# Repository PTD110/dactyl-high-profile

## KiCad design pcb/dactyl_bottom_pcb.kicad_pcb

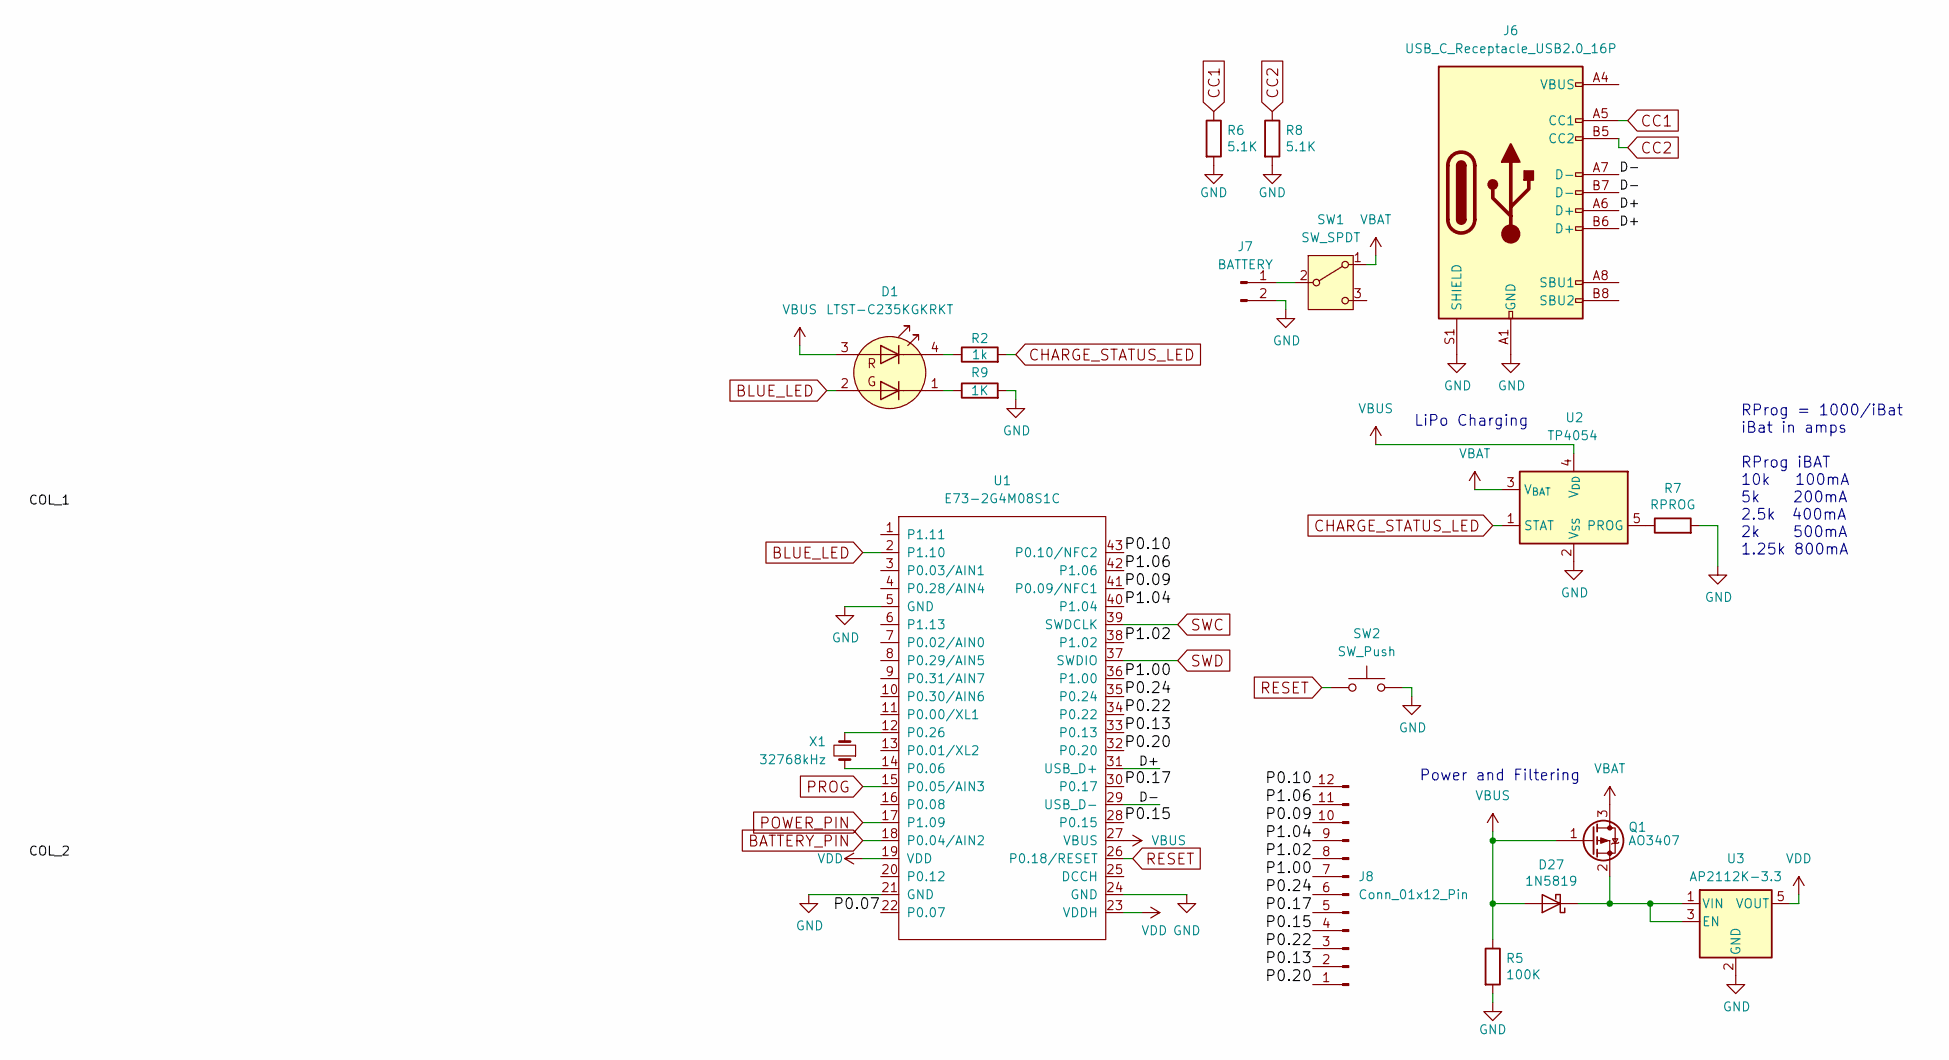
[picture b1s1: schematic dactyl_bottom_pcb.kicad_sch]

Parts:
D1: LTST-C235KGKRKT; LED_LiteOn_LTST-C235KGKRKT
D27: 1N5819; D_SOD-323F
J6: USB_C_Receptacle_USB2.0_16P; USB_C_Receptacle_GCT_USB4105-xx-A_16P_TopMnt_Horizontal
J7: BATTERY; JST_PH_S2B-PH-SM4-TB_1x02-1MP_P2.00mm_Horizontal
J8: Conn_01x12_Pin; JST_SH_SM12B-SRSS-TB_1x12-1MP_P1.00mm_Horizontal
Q1: AO3407; SOT-23
R2: 1k; R_0603_1608Metric_Pad0.98x0.95mm_HandSolder
R5: 100K; R_0603_1608Metric
R6, R8: 5.1K; R_0603_1608Metric
R7: RPROG; R_0603_1608Metric
R9: 1K; R_0603_1608Metric
SW1: SW_SPDT; SW_SP3T_PCM13
SW2: SW_Push; SW_Push_SPST_NO_Alps_SKRK
U1: E73-2G4M08S1C; E73-2G4M08S1C-52840
U2: TP4054; SOT-23-5
U3: AP2112K-3.3; SOT-23-5
X1: 32768kHz

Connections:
/D+: J6.A6 (D+), J6.B6 (D+), U1.31 (USB_D+)
/D-: J6.A7 (D-), J6.B7 (D-), U1.29 (USB_D-)
/P0.07: U1.22 (P0.07)
/P0.09: J8.10, U1.41 (P0.09/NFC1)
/P0.10: J8.12, U1.43 (P0.10/NFC2)
/P0.13: J8.2, U1.33 (P0.13)
/P0.15: J8.4, U1.28 (P0.15)
/P0.17: J8.5, U1.30 (P0.17)
/P0.20: J8.1, U1.32 (P0.20)
/P0.22: J8.3, U1.34 (P0.22)
/P0.24: J8.6, U1.35 (P0.24)
/P1.00: J8.7, U1.36 (P1.00)
/P1.02: J8.8, U1.38 (P1.02)
/P1.04: J8.9, U1.40 (P1.04)
/P1.06: J8.11, U1.42 (P1.06)
BATTERY_PIN: U1.18 (P0.04/AIN2)
BLUE_LED: D1.2 (A2), U1.2 (P1.10)
CC1: J6.A5 (CC1), R6.1
CC2: J6.B5 (CC2), R8.1
CHARGE_STATUS_LED: R2.2, U2.1 (STAT)
GND: J6.A1 (GND), J6.A12 (GND), J6.B1 (GND), J6.B12 (GND), J6.S1 (SHIELD), J7.2, R5.2, R6.2, R7.2, R8.2, R9.2, SW2.2, U1.5 (GND), U1.21 (GND), U1.24 (GND), U2.2 (V_{SS}), U3.2 (GND)
unnamed: D1.4 (K1), R2.1
unnamed: D1.1 (K2), R9.1
unnamed: D27.1 (K), Q1.2 (S), U3.1 (VIN), U3.3 (EN)
unnamed: J6.A4 (VBUS), J6.A9 (VBUS), J6.B4 (VBUS), J6.B9 (VBUS)
unnamed: J7.1, SW1.2 (B)
unnamed: U1.14 (P0.06), X1.1
unnamed: U1.12 (P0.26), X1.2
unnamed: R7.1, U2.5 (PROG)
POWER_PIN: U1.17 (P1.09)
PROG: U1.15 (P0.05/AIN3)
RESET: SW2.1, U1.26 (P0.18/RESET)
SWC: U1.39 (SWDCLK)
SWD: U1.37 (SWDIO)
VBAT: Q1.3 (D), SW1.1 (A), U2.3 (V_{BAT})
VBUS: D1.3 (A1), D27.2 (A), Q1.1 (G), R5.1, U1.27 (VBUS), U2.4 (V_{DD})
VDD: U1.19 (VDD), U1.23 (VDDH), U3.5 (VOUT)

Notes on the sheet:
Power and Filtering
LiPo Charging
RProg = 1000/iBat iBat in amps RProg iBAT 10k 100mA 5k 200mA 2.5k 400mA 2k 500mA 1.25k 800mA

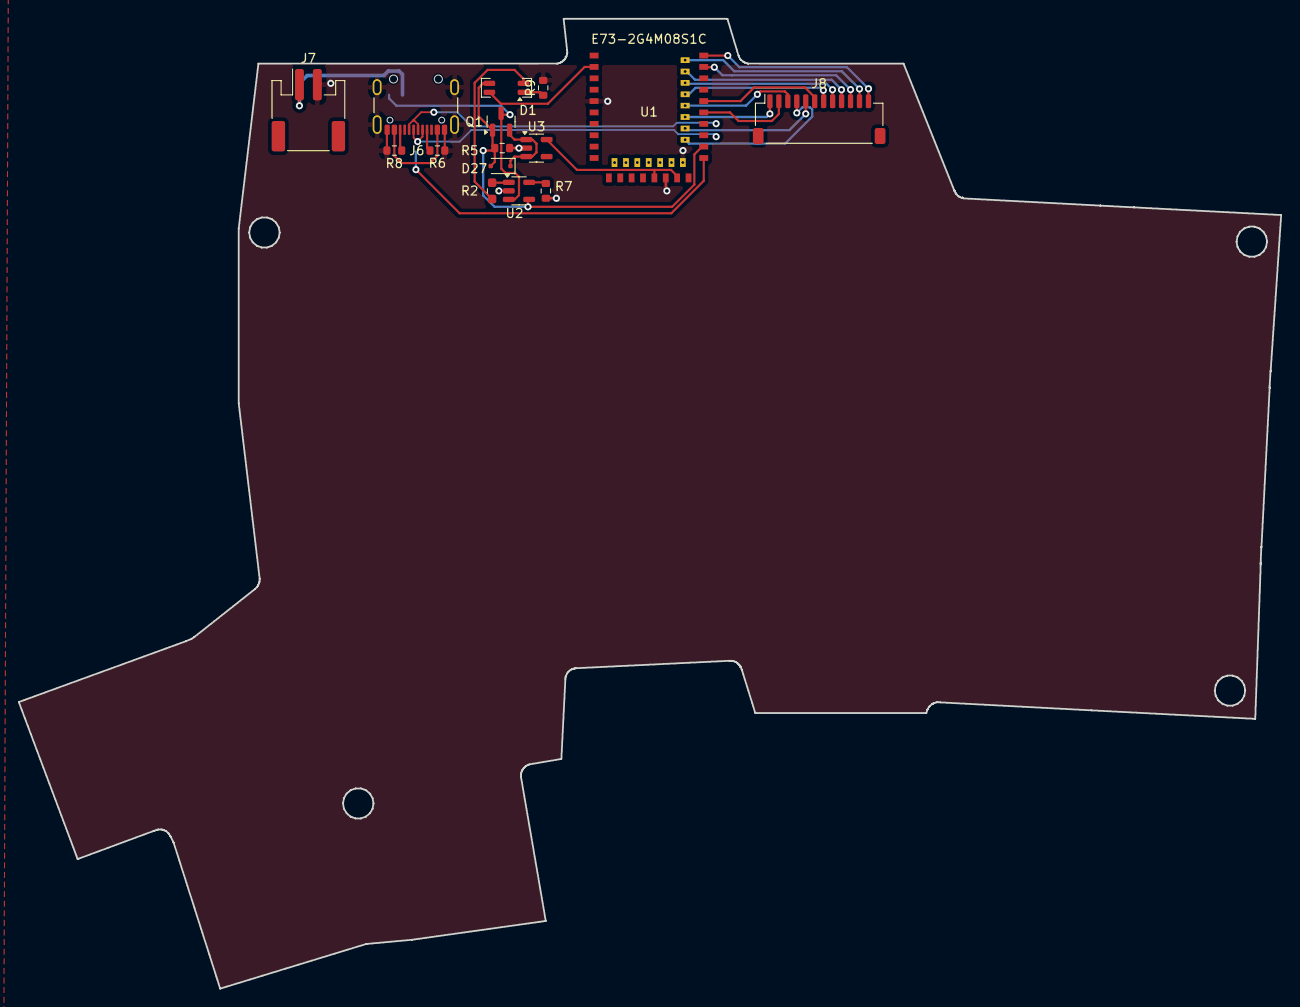
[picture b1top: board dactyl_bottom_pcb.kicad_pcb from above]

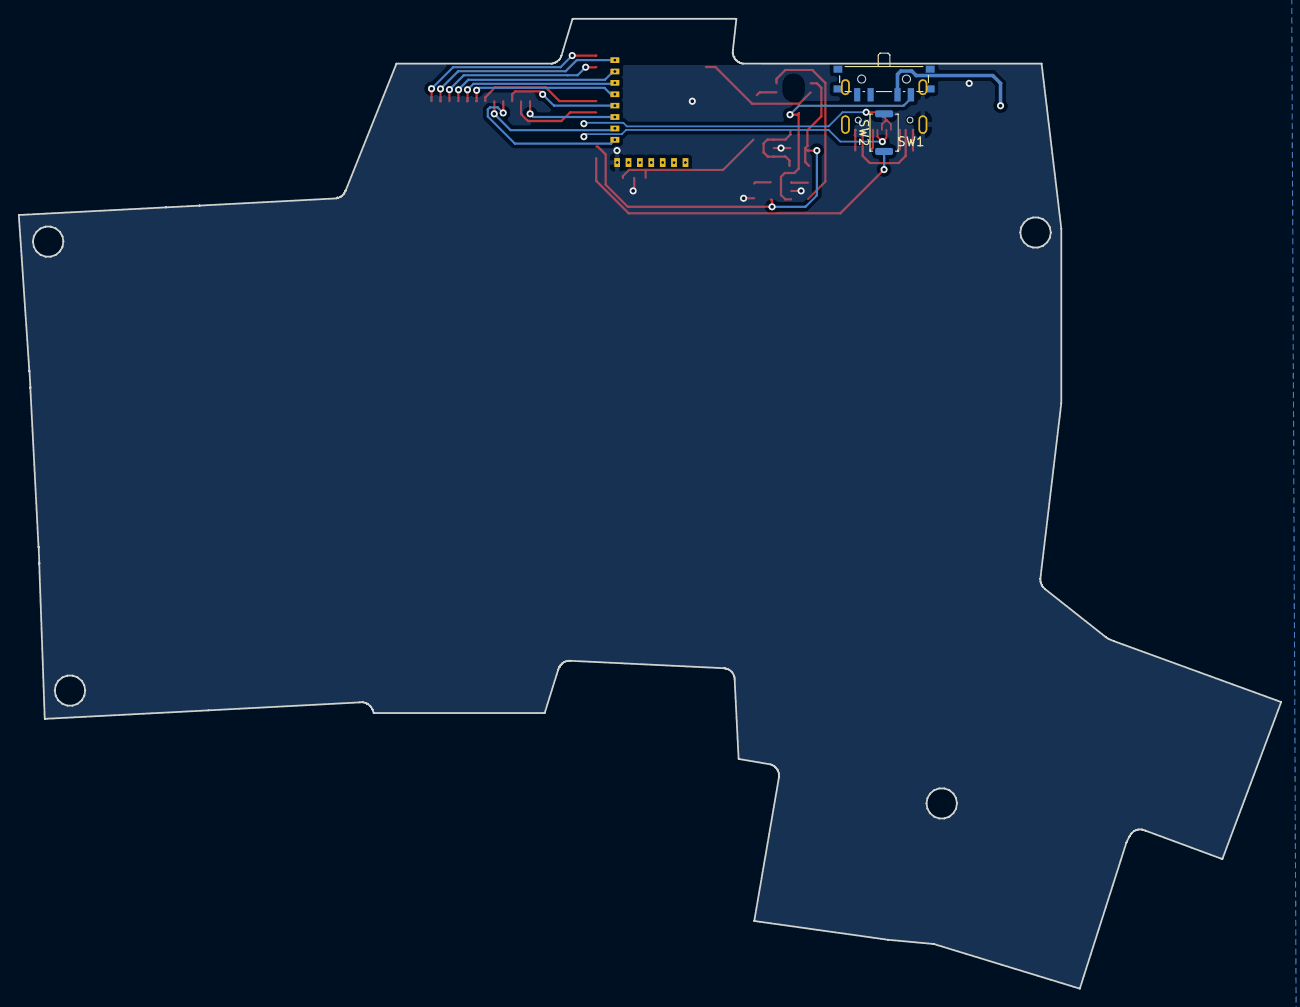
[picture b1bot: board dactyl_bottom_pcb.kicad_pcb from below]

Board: 2 copper layers, 140.9 x 108.2 mm, 17 parts (2 on the bottom side), 29 nets.

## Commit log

2024-05-13 tweaks to mounting holes
2024-05-13 add PCB files
